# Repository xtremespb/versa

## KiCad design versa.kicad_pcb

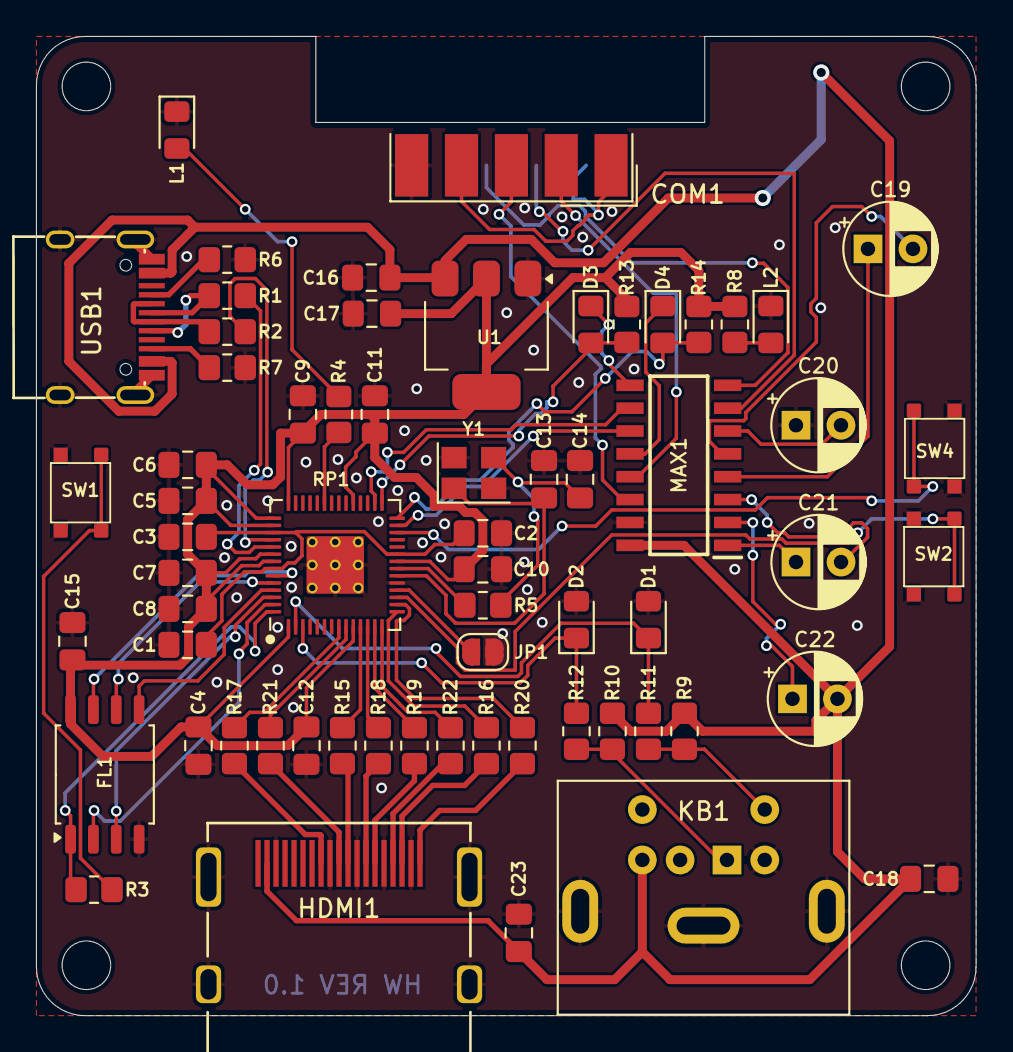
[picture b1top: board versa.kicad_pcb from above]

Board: 2 copper layers, 52.2 x 54.4 mm, 68 parts (0 on the bottom side), 63 nets.

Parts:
C1, C2, C4, C6, C7, C8, C9, C10, C11, C12, C15: 100n; Medved_C_0805
C3, C5: 1u; Medved_C_0805
C13, C14: 15p; Medved_C_0805
C16, C17: 10u; Medved_C_0805
C18, C23: 0.1u; Medved_C_0805
C19, C20, C21, C22: 1u; Medved_CP_Radial_D5.0mm_P2.50mm
COM1: RS232; DSUB-9
D1, D2: 3V3; Medved_D_0805
D3, D4: 1N4148; Medved_D_0805
FL1: W25Q128JVS; Medved_SOIC-8_5.23x5.23mm_P1.27mm
H1, H2, H3, H4: MountingHole; MountingHole_2.7mm
HDMI1: HDMI
JP1: HDMI_DEF; Medved_Jumper_Solder
KB1: PS/2; Connector_Mini-DIN_Female_6Pin_2rows
L1: LED; Medved_L_0805
L2: GREEN; Medved_L_0805
MAX1: MAX232CSE+; SOIC127P600X175-16N
R1, R2: 27; Medved_R_0805
R3, R5, R9, R10: 1k; Medved_R_0805
R4, R8, R13, R14: 1K; Medved_R_0805
R6, R7: 5.1K; Medved_R_0805
R11, R12: 100R; Medved_R_0805
R15, R16, R17, R18, R19, R20, R21, R22: 270R; Medved_R_0805
RP1: RP2040; RP2040-QFN-56
SW1: Flash Button; Button_SMD_3x3x2
SW2: Button; Button_SMD_3x3x2
SW4: Reset Button; Button_SMD_3x3x2
U1: NCP1117-3.3_SOT223; Medved_SOT-223-3_TabPin2
USB1: USB Type C; USB-TYPE-C-31-M-12_lib2
Y1: 12 MHz; Medved_CRYSTAL_3225

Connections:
+3V3: C4.1, C5.1, C6.1, C7.1, C8.1, C9.1, C10.1, C11.1, C12.1, C15.1, C17.1, FL1.8 (VCC), R8.2, R13.2, R14.2, RP1.1 (IOVDD), RP1.10 (IOVDD), RP1.22 (IOVDD), RP1.33 (IOVDD), RP1.42 (IOVDD), RP1.43 (ADC_AVDD), RP1.44 (VREG_IN), RP1.48 (USB_VDD), RP1.49 (IOVDD), U1.2 (VO)
/BTN_DEF: RP1.17 (GPIO14), SW2.3, SW2.4
/CTS_PICO: D3.2 (A), R13.1, RP1.29 (GPIO18)
/D+: R1.1, USB1.6 (DP1), USB1.8 (DP2)
/D-: R2.1, USB1.5 (DN2), USB1.7 (DN1)
/HDMI_CLKN: R17.2, RP1.8 (GPIO6)
/HDMI_CLKP: R21.2, RP1.9 (GPIO7)
/HDMI_D0N: R15.2, RP1.11 (GPIO8)
/HDMI_D0P: R18.2, RP1.12 (GPIO9)
/HDMI_D1N: R19.2, RP1.13 (GPIO10)
/HDMI_D1P: R22.2, RP1.14 (GPIO11)
/HDMI_D2N: R16.2, RP1.15 (GPIO12)
/HDMI_D2P: R20.2, RP1.16 (GPIO13)
/JMP_HDMI: JP1.1 (A), RP1.18 (GPIO15)
/PS2_CLK: D1.1 (K), R11.2, RP1.2 (GPIO0)
/PS2_DATA: D2.1 (K), R12.2, RP1.3 (GPIO1)
/RP2040/GPIO25: R4.2, RP1.37 (GPIO25)
/RP2040/QSPI_SCLK: FL1.6 (CLK), RP1.52 (QSPI_SCLK)
/RP2040/QSPI_SD0: FL1.5 (DI(IO0)), RP1.53 (QSPI_SD0)
/RP2040/QSPI_SD1: FL1.2 (DO(IO1)), RP1.55 (QSPI_SD1)
/RP2040/QSPI_SD2: FL1.3 (IO2), RP1.54 (QSPI_SD2)
/RP2040/QSPI_SD3: FL1.7 (IO3), RP1.51 (QSPI_SD3)
/RP2040/QSPI_SS: FL1.1 (~CS), R3.1, RP1.56 (QSPI_SS)
/RP2040/XIN: C13.1, RP1.20 (XIN), Y1.1
/RP2040/XOUT: R5.1, RP1.21 (XOUT)
/RP2040/~USB_BOOT: R3.2, SW1.3, SW1.4
/RS232/C1+: C21.1, MAX1.1 (C1+)
/RS232/C1-: C21.2, MAX1.3 (C1-)
/RS232/C2+: C19.1, MAX1.4 (C2+)
/RS232/C2-: C19.2, MAX1.5 (C2-)
/RS232/CTS_IN: COM1.7, MAX1.7 (T2OUT)
/RS232/CTS_MAX: D3.1 (K), MAX1.9 (R2OUT)
/RS232/RTS_IN: COM1.8, MAX1.8 (R2IN)
/RS232/RX_IN: COM1.3, MAX1.14 (T1OUT)
/RS232/RX_MAX: D4.1 (K), MAX1.12 (R1OUT)
/RS232/TX_IN: COM1.2, MAX1.13 (R1IN)
/RS232/V+: C22.1, MAX1.2 (V+)
/RS232/V-: C20.2, MAX1.6 (V-)
/RTS_PICO: MAX1.10 (T2IN), RP1.30 (GPIO19)
/RUN: RP1.26 (RUN), SW4.3, SW4.4
/RX_PICO: D4.2 (A), R14.1, RP1.28 (GPIO17)
/TX_PICO: MAX1.11 (T1IN), RP1.27 (GPIO16)
GND: C1.2, C2.2, C3.2, C4.2, C5.2, C6.2, C7.2, C8.2, C9.2, C10.2, C11.2, C12.2, C13.2, C14.2, C15.2, C16.2, C17.2, C18.2, C20.1, C23.2, COM1.5, D1.2 (A), D2.2 (A), FL1.4 (GND), HDMI1.2 (G_D2), HDMI1.5 (G_D1), HDMI1.8 (G_D0), HDMI1.11 (G_CLK), HDMI1.17 (G_DDC/CEC), HDMI1.20 (SHIELD1), HDMI1.21 (SHIELD2), HDMI1.22 (SHIELD3), HDMI1.23 (SHIELD4), JP1.2 (B), KB1.3, L1.1 (K), L2.1 (K), MAX1.15 (GND), R6.1, R7.1, RP1.19 (TESTEN), RP1.57 (GND), SW1.1, SW1.2, SW2.1, SW2.2, SW4.1, SW4.2, U1.1 (GND), USB1.1 (GND), USB1.12 (GND), USB1.13 (SHIELD), Y1.2, Y1.4
unnamed: C14.1, R5.2, Y1.3
unnamed: COM1.1, COM1.4, COM1.6
unnamed: HDMI1.12 (CLKN), R17.1
unnamed: HDMI1.10 (CLKP), R21.1
unnamed: HDMI1.9 (D0N), R15.1
unnamed: HDMI1.7 (D0P), R18.1
unnamed: HDMI1.6 (D1N), R19.1
unnamed: HDMI1.4 (D1P), R22.1
unnamed: HDMI1.3 (D2N), R16.1
unnamed: HDMI1.1 (D2P), R20.1
unnamed: KB1.1, R10.2, R12.1
unnamed: KB1.5, R9.2, R11.1
unnamed: L1.2 (A), R4.1
unnamed: L2.2 (A), R8.1
unnamed: R2.2, RP1.46 (USB_DM)
unnamed: R1.2, RP1.47 (USB_DP)
unnamed: C1.1, C2.1, C3.1, RP1.23 (DVDD), RP1.45 (VREG_VOUT), RP1.50 (DVDD)
unnamed: R6.2, USB1.4 (CC1)
unnamed: R7.2, USB1.10 (CC2)
VBUS: C16.1, C18.1, C22.2, C23.1, HDMI1.18 (+5V), KB1.4, MAX1.16 (VCC), R9.1, R10.1, U1.3 (VI), USB1.2 (VBUS), USB1.11 (VBUS)

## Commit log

2024-12-28 Initial commit (HW Rev 1.0)
2024-12-28 Revert "Initial commit (HW Rev 1.0)"
    This reverts commit 90aa27208cb50b1c65ff2a7ecfcf43725eaa528b.
2024-12-28 Reapply "Initial commit (HW Rev 1.0)"
    This reverts commit bb2d2dc9ae6202f09eef042ee63a253ee042a0c9.
2024-12-28 Minor changes
2024-12-28 Updated silkscreen
